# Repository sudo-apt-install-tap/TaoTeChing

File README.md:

# Tao Te Ching

Split keyboard. Ortholinear grid with column stagger. Built for comfort and long sessions.

---

## Overview
Tao Te Ching is a **split mechanical keyboard** that combines the predictability of ortholinear rows with the ergonomics of column stagger. Each half is compact, symmetric, and designed to keep hands in a neutral position.

### Why?
This will be my first split keyboard. Ive seen many people make splits. But nearly noone uses custom layout. So I made this layout.

### How?
You can write up a simple firmware or use the KMK script in my repo.

---

## Layout
- Split, mirrored halves  
- Ortholinear rows with column stagger  
- Compact layout with outer thumb/utility keys  
- Optimized for touch typing and minimal finger travel

See renders and PCB files for exact spacing and geometry.

---

## Index:
- [Build Guide](https://github.com/sudo-apt-install-tap/TaoTeChing/blob/main/Build%20guide.md)
- [Build Images](https://github.com/sudo-apt-install-tap/TaoTeChing/blob/main/README.md#build-images)
- [Journal](tao-te-ching-journal.md)
- [Images](Images)
- [PCB](PCB)
- [Fimware](firmware)
- [CAD](CAD)
  
---

## Hardware
- MX-compatible switches  
- Per-key diodes (matrix)  
- Controller footprint suitable for XIAO-class boards  
- Board-to-board connection pads for split communication

Plates can be 3D-printed (PLA works) or CNCed.

---

## Firmware
Designed to work with common keyboard firmware:
- QMK / KMK / ZMK (controller-dependent)
I will use KMK

---

## Renders
- KiCAD Render: <br>
  
- CAD Exploded: <br>
  
- CAD Assembled: <br>
  
- Left Case: <br>
  
- Right Case: <br>
  
- Left Plate: <br>
  
- Right Plate: <br>

---

## KiCAD Images
- Layout: <br>
  
- Left Sheet: <br>
  
- Right Sheet: <br>
  
- Wiring: <br>

---

## Project Status
- [x] Layout: finalized  
- [x] PCB: routed and rendered  
- [x] Prototypes: Done!
- [x] Revisions: Done!

### DONE!!

---

## Build Images And Videos
<div align="center">

 <br><br>
 <br><br>
 <br><br>
<br><br>
<br><br>
<br><br>
<br><br>

[TAO TE CHING DEMO](https://www.youtube.com/shorts/A5UJ3Mnc8bE)

</div>

---

# Bill of Materials (BOM)

| Item | Description | Cost (INR) |
|------|-------------|----------:|
| Keycaps | Full keycap set | ₹1,400 |
| PCB | Custom PCB fabrication | ₹3,726 |
| Switches | Mechanical keyboard switches | ₹1,275 |
| Diodes | Per-key matrix diodes | ₹102 |
| MCU | Seeed Studio XIAO RP2040 | ₹1,236 |
| Case & Plate | 3D printed case and plate (shipping included) | ₹500 |
| **Total** |  | **₹8,239** |

> **Project Cost:** ₹8,239 (~$95 USD)

## CAD SOURCE FILES AVAILABLE!

[ONSHAPE](https://cad.onshape.com/documents/3a64b1ece82f2d5ea6875226/w/4aeac85fe30a56c6319ae754/e/e0c4af6436b0f9ae25f54182?renderMode=0&uiState=699d1a8bab682d7d1a6430e0)

---

## License
Open source. Build it, modify it, improve it.

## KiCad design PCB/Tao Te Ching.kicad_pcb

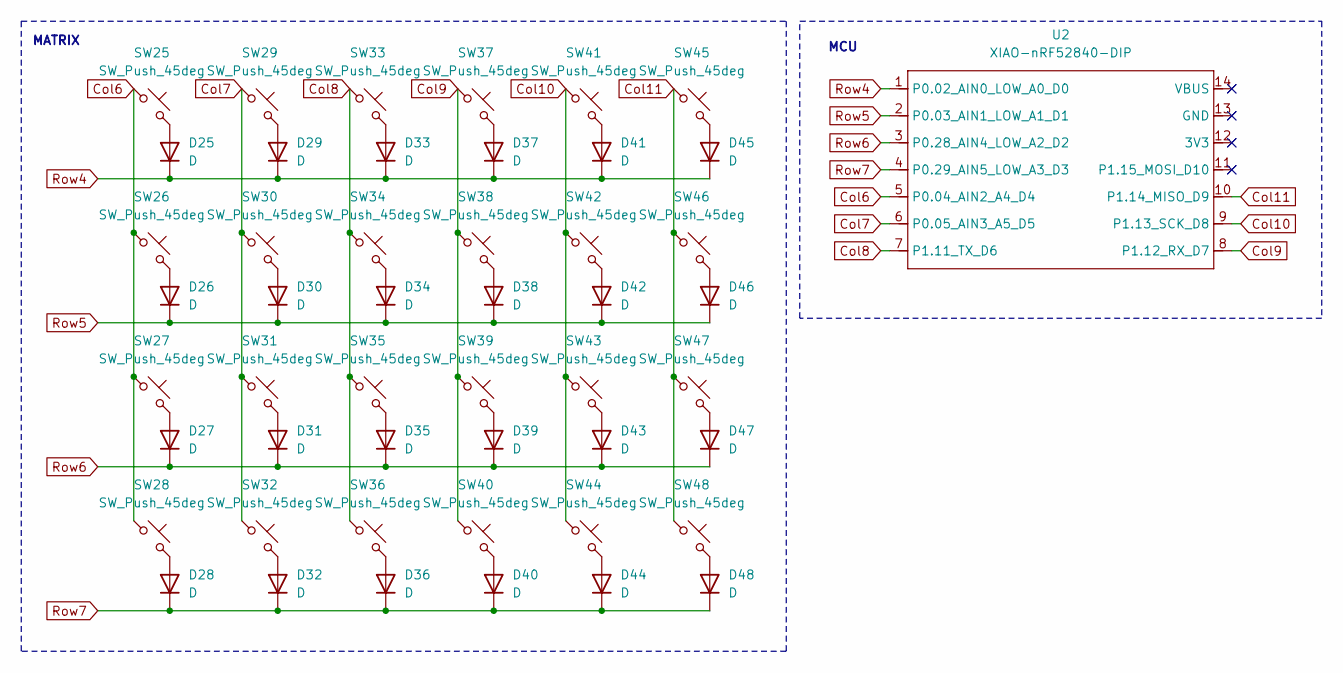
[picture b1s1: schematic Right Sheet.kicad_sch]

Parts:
D25, D26, D27, D28, D29, D30, D31, D32, D33, D34, D35, D36, D37, D38, D39, D40, D41, D42, D43, D44, D45, D46, D47, D48: D; D_SOD-123
SW25, SW26, SW27, SW28, SW29, SW30, SW31, SW32, SW33, SW34, SW35, SW36, SW37, SW38, SW39, SW40, SW41, SW42, SW43, SW44, SW45, SW46, SW47, SW48: SW_Push_45deg; SW_Hotswap_Kailh_MX
U2: XIAO-nRF52840-DIP

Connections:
Col6: SW25.1, SW26.1, SW27.1, SW28.1, U2.5 (P0.04_AIN2_A4_D4)
Col7: SW29.1, SW30.1, SW31.1, SW32.1, U2.6 (P0.05_AIN3_A5_D5)
Col8: SW33.1, SW34.1, SW35.1, SW36.1, U2.7 (P1.11_TX_D6)
Col9: SW37.1, SW38.1, SW39.1, SW40.1, U2.8 (P1.12_RX_D7)
Col10: SW41.1, SW42.1, SW43.1, SW44.1, U2.9 (P1.13_SCK_D8)
Col11: SW45.1, SW46.1, SW47.1, SW48.1, U2.10 (P1.14_MISO_D9)
unnamed: D25.2 (A), SW25.2
unnamed: D26.2 (A), SW26.2
unnamed: D27.2 (A), SW27.2
unnamed: D28.2 (A), SW28.2
unnamed: D29.2 (A), SW29.2
unnamed: D30.2 (A), SW30.2
unnamed: D31.2 (A), SW31.2
unnamed: D32.2 (A), SW32.2
unnamed: D33.2 (A), SW33.2
unnamed: D34.2 (A), SW34.2
unnamed: D35.2 (A), SW35.2
unnamed: D36.2 (A), SW36.2
unnamed: D37.2 (A), SW37.2
unnamed: D38.2 (A), SW38.2
unnamed: D39.2 (A), SW39.2
unnamed: D40.2 (A), SW40.2
unnamed: D41.2 (A), SW41.2
unnamed: D42.2 (A), SW42.2
unnamed: D43.2 (A), SW43.2
unnamed: D44.2 (A), SW44.2
unnamed: D45.2 (A), SW45.2
unnamed: D46.2 (A), SW46.2
unnamed: D47.2 (A), SW47.2
unnamed: D48.2 (A), SW48.2
Row4: D25.1 (K), D29.1 (K), D33.1 (K), D37.1 (K), D41.1 (K), D45.1 (K), U2.1 (P0.02_AIN0_LOW_A0_D0)
Row5: D26.1 (K), D30.1 (K), D34.1 (K), D38.1 (K), D42.1 (K), D46.1 (K), U2.2 (P0.03_AIN1_LOW_A1_D1)
Row6: D27.1 (K), D31.1 (K), D35.1 (K), D39.1 (K), D43.1 (K), D47.1 (K), U2.3 (P0.28_AIN4_LOW_A2_D2)
Row7: D28.1 (K), D32.1 (K), D36.1 (K), D40.1 (K), D44.1 (K), D48.1 (K), U2.4 (P0.29_AIN5_LOW_A3_D3)

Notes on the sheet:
MATRIX
MCU

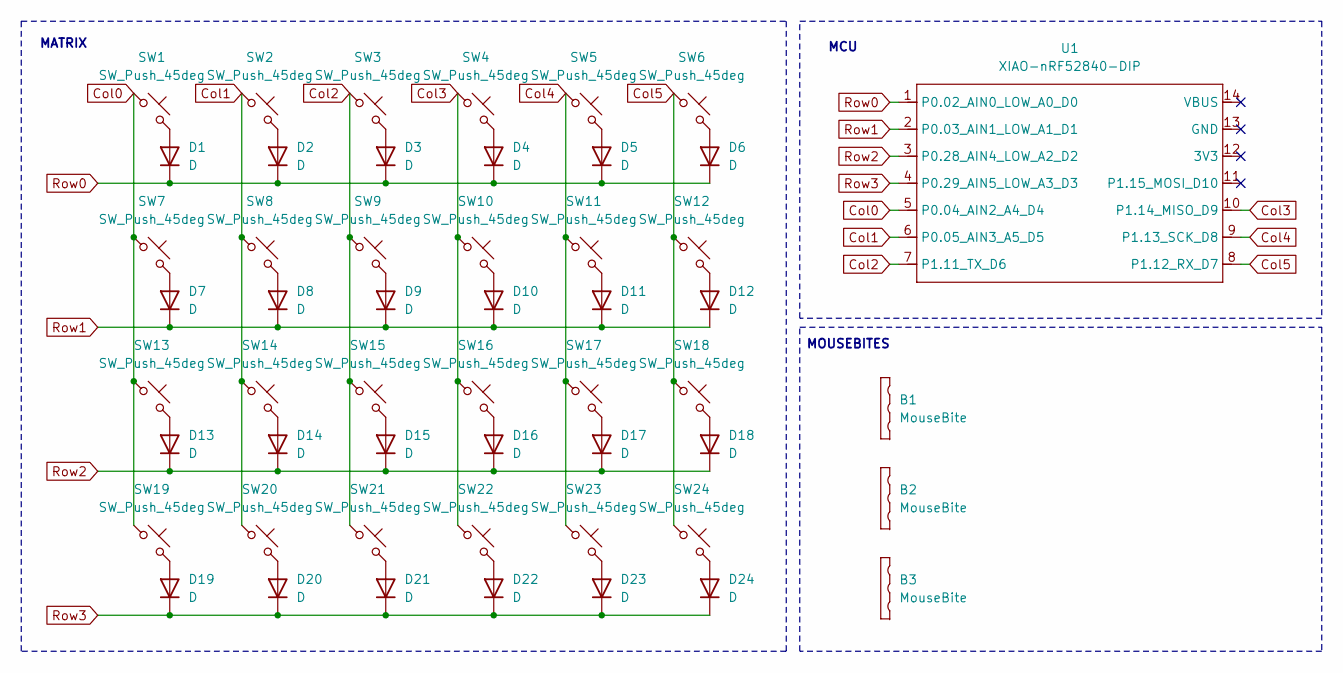
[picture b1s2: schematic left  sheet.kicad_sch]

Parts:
B1, B2, B3: MouseBite; MouseBite-Slot_2.0x2.0mm_outset_D0.5mm_P0.85mm_3h
D1, D2, D3, D4, D5, D6, D7, D8, D9, D10, D11, D12, D13, D14, D15, D16, D17, D18, D19, D20, D21, D22, D23, D24: D; D_SOD-123
SW1, SW2, SW3, SW4, SW5, SW6, SW7, SW8, SW9, SW10, SW11, SW12, SW13, SW14, SW15, SW16, SW17, SW18, SW19, SW20, SW21, SW22, SW23, SW24: SW_Push_45deg; SW_Hotswap_Kailh_MX
U1: XIAO-nRF52840-DIP

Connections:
Col0: SW1.1, SW7.1, SW13.1, SW19.1, U1.5 (P0.04_AIN2_A4_D4)
Col1: SW2.1, SW8.1, SW14.1, SW20.1, U1.6 (P0.05_AIN3_A5_D5)
Col2: SW3.1, SW9.1, SW15.1, SW21.1, U1.7 (P1.11_TX_D6)
Col3: SW4.1, SW10.1, SW16.1, SW22.1, U1.10 (P1.14_MISO_D9)
Col4: SW5.1, SW11.1, SW17.1, SW23.1, U1.9 (P1.13_SCK_D8)
Col5: SW6.1, SW12.1, SW18.1, SW24.1, U1.8 (P1.12_RX_D7)
unnamed: D1.2 (A), SW1.2
unnamed: D2.2 (A), SW2.2
unnamed: D3.2 (A), SW3.2
unnamed: D4.2 (A), SW4.2
unnamed: D5.2 (A), SW5.2
unnamed: D6.2 (A), SW6.2
unnamed: D7.2 (A), SW7.2
unnamed: D8.2 (A), SW8.2
unnamed: D9.2 (A), SW9.2
unnamed: D10.2 (A), SW10.2
unnamed: D11.2 (A), SW11.2
unnamed: D12.2 (A), SW12.2
unnamed: D13.2 (A), SW13.2
unnamed: D14.2 (A), SW14.2
unnamed: D15.2 (A), SW15.2
unnamed: D16.2 (A), SW16.2
unnamed: D17.2 (A), SW17.2
unnamed: D18.2 (A), SW18.2
unnamed: D19.2 (A), SW19.2
unnamed: D20.2 (A), SW20.2
unnamed: D21.2 (A), SW21.2
unnamed: D22.2 (A), SW22.2
unnamed: D23.2 (A), SW23.2
unnamed: D24.2 (A), SW24.2
Row0: D1.1 (K), D2.1 (K), D3.1 (K), D4.1 (K), D5.1 (K), D6.1 (K), U1.1 (P0.02_AIN0_LOW_A0_D0)
Row1: D7.1 (K), D8.1 (K), D9.1 (K), D10.1 (K), D11.1 (K), D12.1 (K), U1.2 (P0.03_AIN1_LOW_A1_D1)
Row2: D13.1 (K), D14.1 (K), D15.1 (K), D16.1 (K), D17.1 (K), D18.1 (K), U1.3 (P0.28_AIN4_LOW_A2_D2)
Row3: D19.1 (K), D20.1 (K), D21.1 (K), D22.1 (K), D23.1 (K), D24.1 (K), U1.4 (P0.29_AIN5_LOW_A3_D3)

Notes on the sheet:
MOUSEBITES
MATRIX
MCU

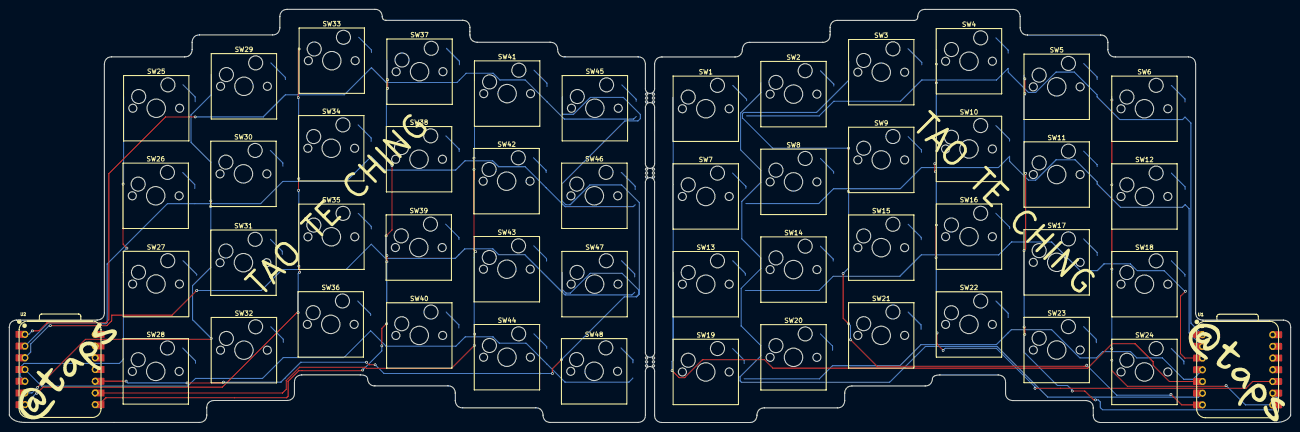
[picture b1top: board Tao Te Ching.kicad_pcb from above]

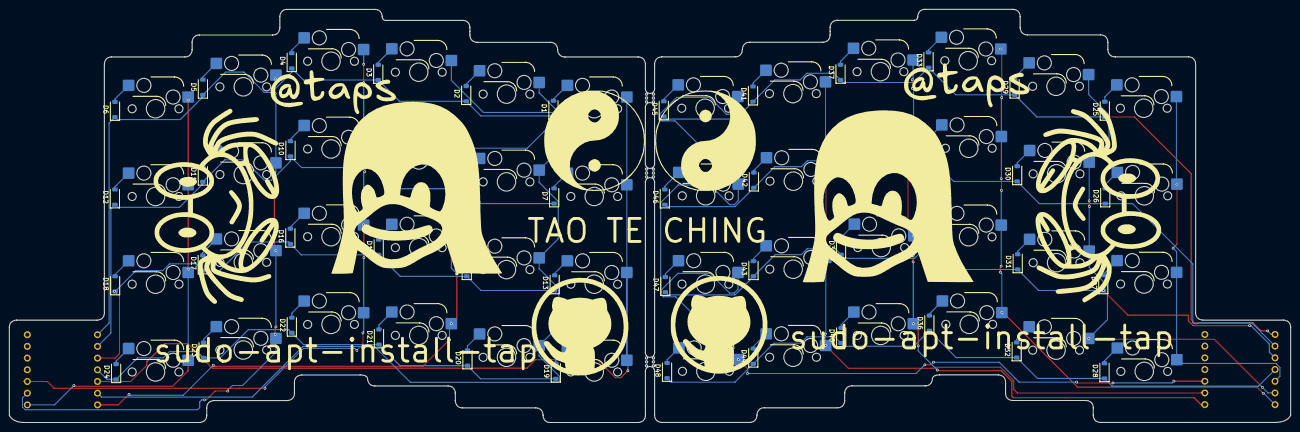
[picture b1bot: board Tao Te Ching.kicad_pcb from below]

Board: 2 copper layers, 278.2 x 89.7 mm, 101 parts (48 on the bottom side), 68 nets.

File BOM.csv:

"Id";"Designator";"Footprint";"Quantity";"Designation";"Supplier and ref";
1;"D22,D38,D41,D42,D44,D19,D25,D39,D40,D23,D16,D18,D35,D24,D17,D14,D48,D32,D27,D5,D13,D29,D28,D7,D6,D8,D1,D45,D21,D46,D43,D33,D15,D10,D34,D4,D30,D3,D37,D2,D36,D20,D26,D12,D11,D47,D31,D9";"D_SOD-123";48;"D";;;
2;"SW17,SW30,SW38,SW12,SW33,SW23,SW46,SW28,SW45,SW13,SW24,SW44,SW35,SW2,SW42,SW20,SW22,SW43,SW11,SW4,SW47,SW36,SW9,SW41,SW26,SW39,SW48,SW18,SW6,SW7,SW15,SW1,SW5,SW27,SW8,SW31,SW21,SW40,SW16,SW37,SW14,SW29,SW10,SW32,SW3,SW34,SW25,SW19";"SW_Cherry_MX_1.00u_PCB";48;"SW_Push_45deg";;;
3;"U1,U2";"XIAO-nRF52840-DIP";2;"XIAO-nRF52840-DIP";;;

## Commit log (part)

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2026-02-07 Updated PCB and Added /Images
2026-02-09 Reworked Case and images
2026-02-09 Add README for Tao Te Ching keyboard project
2026-02-09 Enhance README with motivation and additional images
    Added sections on project motivation, firmware usage, and KiCAD images.
2026-02-09 Added silkscreen art
2026-02-10 Added firmware
2026-02-10 Add Bill Of Materials to README
    Added Bill Of Materials section with cost breakdown.
2026-02-10 Added Cart images
2026-02-24 Add CAD source files section to README
    Added a section for CAD source files with a link to Onshape.
2026-02-26 Added hotswap sockets
2026-03-12 Added Case STLs
2026-03-15 Updated Firmware
2026-03-16 Create build guide for Tao Te Ching keyboard
    Added a comprehensive build guide for the Tao Te Ching keyboard, including required tools, recommended build order, and detailed instructions for soldering components.
2026-03-16 Enhance README with index and layout details
    Added index section and improved layout details.
2026-03-16 Revise README with project status and images
    Updated README.md to reflect project status and additional images.
2026-03-16 Update README with additional information and images
2026-03-16 Added Journal from Blueprint!
2026-03-16 Update README.md with additional sections and links
2026-05-21 Refactor journal entries for keyboard project
    Updated journal entries with improved formatting and additional details about the keyboard project.
2026-05-21 Refactor JOURNAL.md with local image paths
    Updated images in the journal to local paths and revised text for clarity.
2026-05-22 Standardize time spent format in JOURNAL.md
    Updated total time spent entries for various project milestones to a more consistent format.
2026-05-22 Update JOURNAL.md by removing date header
    Removed the journal date header for clarity.
2026-05-31 Refactor image syntax in JOURNAL.md
    Updated images and formatting in the JOURNAL.md file, replacing Markdown image syntax with HTML image tags for better display.
2026-06-05 Update README.md with project details and images
2026-06-05 Update JOURNAL.md with troubleshooting notes and images
    Added multiple images and updated journal entry with troubleshooting details.
2026-06-10 Revise JOURNAL.md with project updates and details
    Updated JOURNAL.md with detailed entries on the keyboard project, including schematic, PCB routing, case design, artwork addition, and assembly progress. Enhanced clarity and structure throughout the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
